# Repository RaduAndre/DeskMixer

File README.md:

# DeskMixer 🎛️

<div align="center">

A **low latency** physical volume mixer with programmable buttons for Windows, inspired by [Deej](https://github.com/omriharel/deej).

**Control your audio with near-instant response and automate actions with real hardware - fully scalable to your needs!**

[Features](#-features) • [Hardware](#-hardware) • [Installation](#-installation) • [Configuration](#-configuration) • [Building](#-building-from-source)

</div>

---

## 🚀 Get Started 

**For Windows users, the simplest way to get up and running is with the pre-compiled executable!**

1.  **Download:** Go to the [**Releases Page**](/RaduAndre/DeskMixer/releases) and download the latest `DeskMixer.exe` file. (no instalation needed)
2. **Configure:** Follow the steps in the [Configuration](#-configuration) section to bind your sliders and program your buttons!

---

## 📸 Gallery

### Modern Software Interface

DeskMixer features a sleek, modern interface with a dark theme and smooth animations designed for intuitive hardware control.

*Clean, modern interface with volume sliders and programmable action buttons*

*Sliding configuration menu for easy customization*

#### Interface Features

**Visual Design:**
- 🎨 **Modern Interface**: Premium glassmorphic design with **customizable accent colors** and animations
- 🪟 **Frameless Window**: Custom title bar with drag-to-move functionality
- 📐 **Scalable Layout**: Automatically adapts to any number of sliders and buttons
- ✨ **Smooth Animations**: Fluid transitions and visual feedback for all interactions

**Volume Sliders:**
- 🎛️ **Visual Scale Indicators**: Each slider displays a scale icon showing the full range
- 🏷️ **Smart Labels**: Automatically display bound applications (e.g., "Master + Spotify")
- 💚 **Hardware Sync**: Sliders animate smoothly when adjusted via hardware with green highlight feedback
- 🔄 **Drag-and-Drop Reordering**: Rearrange sliders to match your preferred layout
- 🖱️ **Click-to-Configure**: Click any slider to open its configuration menu

**Action Buttons:**
- 🎮 **Customizable Grid**: Arrange buttons in any grid size (rows × columns)
- 🔵 **Active State Indicators**: Blue highlight shows which buttons are configured
- ⚡ **Hardware Feedback**: Buttons flash when pressed on the physical device
- 🔄 **Drag-and-Drop**: Reorder buttons including empty placeholder positions
- 📝 **Dynamic Labels**: Button text adjusts to show the configured action

**Configuration Menu:**
- 📱 **Sliding Panel**: Smooth slide-in menu from the right side
- 🎯 **Context-Sensitive**: Different menus for sliders, buttons, and settings
- 🔍 **Live Search**: Browse and add applications with file picker integration
- 📋 **Expandable Sections**: Organized categories with collapsible headers
- ✅ **Visual Selection**: Active bindings highlighted with checkmarks

**Settings & Customization:**
- ⚙️ **General Settings**: Start hidden, Windows startup integration, slider sampling modes
- 📐 **Layout Controls**: Configure button grid dimensions (R×C)
- 🔄 **Reorder Modes**: Toggle swap modes for buttons or sliders independently
- 📊 **Slider Sampling**: Choose between Soft, Normal, or Hard sensitivity modes
- ℹ️ **Version Display**: Build version shown at bottom of settings menu

**Hardware Integration:**
- 🔌 **Real-time Sync**: Slider positions update instantly from hardware movements
- 🎯 **Button Press Feedback**: Visual flash confirms hardware button presses
- 🔄 **Bidirectional Control**: Changes sync between hardware and software
- 🚫 **Read-only Sliders**: UI sliders display-only to prevent conflicts with hardware control

### DIY Hardware Build

*A functional, handcrafted build - proving that professional results don't require a professional workshop!*

---

## ✨ Features

DeskMixer takes physical volume control and supercharges it with macro-like button actions.

### Volume Control
- ⚡ **Low Latency**: Optimized for near-instant response (~10-20ms) with 115200 baud serial communication
- 🎛️ **Physical Sliders**: Control individual application volumes with real hardware sliders
- 📊 **Scalable Design**: Add as many sliders as you need - the software adapts automatically
- 🔊 **Flexible Targets**: Control master volume, microphone, system sounds, or individual apps
- 🎚️ **Adjustable Sensitivity**: Choose between Instant, Responsive, Soft, Normal, or Hard sampling modes
- 💾 **Persistent Settings**: Your configuration is saved between sessions

### Button Actions
- ⌨️ **Custom Keybinds**: Map any keyboard shortcut to physical buttons
- 🎮 **Media Controls**: Play/pause, next/previous track, seek forward/backward
- 🔇 **Mute Controls**: Instant mute/unmute for system, microphone, or specific applications
- 🔀 **Audio Switching**: Switch between audio output devices with a button press
- 🚀 **App Launcher**: Launch or focus applications instantly

### System Integration
- 🪟 **System Tray**: Runs minimized with quick access
- 🔌 **Auto-Detection**: Automatic serial port detection
- 🔄 **Hot-Reload**: Configuration updates in real-time
- 🎯 **Focus Tracking**: Optional control of currently active application

---

## 🎛️ Volume Targets

The software supports multiple volume control modes:

| Target | Description | Use Case |
|--------|-------------|----------|
| 🔊 **Master** | System master volume | Overall volume control |
| 🎤 **Microphone** | Default microphone input | Quick mic adjustments |
| 🔔 **System Sounds** | Windows notification sounds | Silence those pings! |
| ⭐ **Current Application** | Currently focused app | Dynamic control of active app |
| 🎵 **Individual Apps** | Specific applications | Dedicated controls (Spotify, Discord, etc.) |
| ❔ **Unbound** | No assignment | Flexible unassigned slider |
| ❌ **None** | Disabled | Slider inactive |

**Note:** The application list updates automatically based on running audio applications. **The UI scales to accommodate any number of slider bindings you create!**

---

## 🎮 Button Actions

### Media Controls
- ⏯️ **Play/Pause**: Toggle media playback
- ⏭️ **Next Track**: Skip to next media track  
- ⏮️ **Previous Track**: Go to previous media track
- ⏩ **Seek Forward**: Jump forward in current media
- ⏪ **Seek Backward**: Jump backward in current media

### Audio Controls
- 🔊 **Volume Up**: Increase system volume
- 🔉 **Volume Down**: Decrease system volume
- 🔇 **Mute**: Toggle mute for system, microphone, or specific application
- 🔀 **Switch Audio Output**: Switch between available audio output devices*

### Advanced Actions
- ⌨️ **Custom Keybind**: Execute any keyboard shortcut (see [KEYBIND_EXAMPLES.md](KEYBIND_EXAMPLES.md))
- 🚀 **Launch App**: Start or focus specific applications

**Pro Tip:** Combine button actions with specific application targets for powerful workflows. For example:
- Mute Discord specifically with one button
- Launch Spotify and set volume to 50% with another
- Send custom shortcuts to specific apps

**The button configuration UI scales dynamically - add as many buttons as your microcontroller has pins!**

---

## 🔧 Hardware

### Required Components
- **Microcontroller**: ESP32 or compatible Arduino board
- **Sliders**: 4x 10kΩ linear potentiometers (scalable to more)
- **Buttons**: 6x push buttons (scalable to more)
- **Connection**: PCB or breadboard
- **Cable**: USB cable for serial communication

### Default Pin Configuration
You can modify these in the Arduino sketch to match your build:

**Sliders:**
- GPIO 33, 32, 35, 34

**Buttons:**
- GPIO 27, 25, 14, 26, 12, 13

### Expanding Your Build
Want more controls? Simply:
1. Add more potentiometers/buttons to your hardware
2. Update the pin configuration in `arduino/DeskMixer/DeskMixer.ino`
3. Upload the modified firmware
4. The DeskMixer software will automatically detect and configure the new inputs!

### Circuit Explanation

*Wiring diagram showing connections between ESP32, potentiometers, and buttons*

#### Understanding the Circuit

The DeskMixer circuit consists of three main components working together:

**Power Distribution:**
- The ESP32 is powered via USB connection to your computer
- All components share a common ground (GND) connection
- The 3.3V pin from the ESP32 powers the potentiometers

**Potentiometer Connections (Volume Sliders):**
Each potentiometer has three pins:
- **Left pin**: Connected to GND (ground)
- **Middle pin (wiper)**: Connected to ESP32 analog input pins (GPIO 33, 32, 35, 34)
- **Right pin**: Connected to 3.3V power

As you move the slider, the middle pin voltage varies between 0V and 3.3V, which the ESP32 reads as analog values (0-1024). The software then maps these values to volume levels (0-100%).

**Button Connections:**
Each button uses a simple pull-down configuration:
- **One side**: Connected to ESP32 digital input pins (GPIO 27, 25, 14, 26, 12, 13)
- **Other side**: Connected to GND (ground)
- **Internal pull-up resistor**: Enabled in firmware (button reads HIGH when not pressed, LOW when pressed)

**Color Coding in Diagram:**
- **Black**: Ground connections
- **Red**: 3.3V power connections
- **Yellow/Orange/Blue**: Signal wires to ESP32 GPIO pins

#### Important Notes

⚠️ **Analog Pin Limitations**: On ESP32, not all pins support analog reading. Use only ADC1 pins (GPIO 32-39) for potentiometers. Avoid GPIO 25 and 26 for analog input as they're DAC pins.

⚠️ **Voltage Levels**: ESP32 GPIO pins are 3.3V tolerant. Never connect 5V directly to any GPIO pin.

💡 **Wire Gauge**: Use 22-24 AWG wire for connections. Solid core wire works well for breadboard prototyping, while stranded wire is better for the final build.

💡 **Debouncing**: The firmware includes software debouncing for buttons to prevent false triggers. No additional hardware debouncing (capacitors) is needed.

### 3D Models & PCB Files
> **Coming Soon**: 3D printable enclosure models and Gerber files for PCB manufacturing will be added in future updates!

---

## 📦 Installation

### Option 1: Pre-built Executable (Easiest)

1. Download `DeskMixer.exe` from the [Releases](https://github.com/RaduAndre/DeskMixer/releases) page.
2. Run the executable

### Option 2: Run from Source

**Requirements:**
- Python 3.13+
- Arduino IDE
- ESP32 board or compatible Arduino

**Steps:**

1. Clone the repository:
```bash
git clone https://github.com/RaduAndre/DeskMixer.git
cd DeskMixer/src
```

2. Install dependencies:
```bash
pip install -r requirements.txt
```

3. Run the application:
```bash
python main.py
```

### Upload Firmware to Arduino

1. Open `arduino/DeskMixer/DeskMixer.ino` in Arduino IDE
2. Select your board (ESP32) and COM port
3. Upload the sketch
4. The firmware will automatically communicate with DeskMixer

---

## ⚙️ Configuration

### First-Time Setup

1. **Launch DeskMixer**
2. **Connect Hardware**: The application will automatically detect your Arduino's serial port
3. **Configure Sliders**: 
   - Click on any slider to open the configuration menu
   - Select from General options (Master, Microphone, System sounds, Focused application, Unbound)
   - Or choose from Active sounds (currently running applications)
   - Or add custom applications via the search function
   - Multiple applications can be bound to the same slider
4. **Configure Buttons**:
   - Click on any button to open the action menu
   - Select from Media Controls (Play/Pause, Next, Previous, etc.)
   - Configure Mute actions with specific targets
   - Set up custom Keybinds or Launch app actions
   - Changes save automatically

### Slider Configuration

**Binding Options:**
- **General Targets**: Master volume, Microphone, System sounds, Focused application, Unbound
- **Active Sounds**: Dynamically detected running applications with audio
- **Custom Applications**: Add any application via name search or file browser
- **Multiple Bindings**: Bind multiple applications to a single slider for grouped control
- **Smart Labels**: Slider labels automatically update to show all bound applications

**Configuration Menu:**
- Click any slider to open its dedicated configuration menu
- Expandable sections organize options by category
- Active bindings show checkmarks for easy identification
- Right-click custom applications to delete them from the list
- Browse for .exe or .lnk files to add new applications

### Button Configuration

**Available Actions:**

*Media Controls:*
- Play/Pause, Previous, Next
- Volume up/down
- Seek backward/forward

*Advanced Actions:*
- **Mute**: Choose target (Master, Microphone, System sounds, Focused application)
- **Switch Audio Output**: Cycle through devices or select specific output (Speakers, Headphones)
- **Keybind**: Enter custom keyboard shortcuts (see [KEYBIND_EXAMPLES.md](KEYBIND_EXAMPLES.md))
- **Launch app**: Browse and select applications to launch or focus

**Configuration Menu:**
- Click any button to open its action menu
- Expandable items reveal sub-options (e.g., Mute → Master/Microphone/etc.)
- Input fields for Keybind and Launch app actions
- File browser integration for selecting applications
- Active action highlighted with blue indicator

### Layout Customization

**Button Grid:**
- Open Settings menu (gear icon)
- Navigate to Layout → Grid Size
- Enter desired Rows (R) and Columns (C)
- Grid automatically validates against available buttons
- Invalid dimensions flash red with error feedback

**Reordering Elements:**
- Open Settings → Layout → Reorder Elements
- Select "Swap Buttons" or "Swap Sliders" to enter reorder mode
- Drag and drop elements to rearrange them
- Supports sparse layouts (buttons can occupy any grid position)
- Click the reorder option again to exit reorder mode

### Settings Menu

Access via the gear icon in the top-right corner:

**General:**
- **Start Hidden (on tray)**: Launch minimized to system tray
- **Start on Windows startup**: Automatically launch with Windows
- **Slider Sampling**: Adjust hardware response sensitivity
  - **Instant**: Zero-latency mode - no smoothing for immediate response
  - **Responsive**: Minimal smoothing - very fast with slight stabilization
  - **Soft**: Light averaging - balanced response (5 samples)
  - **Normal**: Moderate averaging - smooth control (10 samples)
  - **Hard**: Heavy averaging - very smooth, slower response (20 samples)

**Layout:**
- **Grid Size**: Configure button grid dimensions
- **Accent Color**: Customize the UI with 'Default' (Teal) or any custom color via the picker
- **Reorder Elements**: Enable drag-and-drop for buttons or sliders

### System Tray
- **Double-click** tray icon: Show/hide main window
- **Right-click** tray icon: Quick actions menu
- Window automatically minimizes to tray when closed

---

## 🏗️ Building from Source

Create your own executable using either method:

### PyInstaller (Faster)
```bash
cd src
python build_app.py
```

### Nuitka (More Optimized)
```bash
cd src
python build_nuitka.py
```

Built executables will appear in `src/build/dist/`

---

## 🎨 About the Hardware Build

The device shown in the gallery was handcrafted with basic tools and materials - no fancy workshop required! It's a testament that functional, effective hardware doesn't need to be professionally manufactured. The beauty of this project is in its functionality and the satisfaction of building something yourself.

**DIY Philosophy:** This project embraces the maker spirit - it's about creating tools that work for YOU, not winning beauty contests. If it controls your volume and makes your workflow better, it's perfect.

---

## 🛠️ Customization & Scalability

DeskMixer is designed to grow with your needs:

### Hardware Scaling
- **Start small**: 2 sliders and 2 buttons  
- **Go big**: 16+ sliders and 20+ buttons
- **Mix it up**: Combine sliders, buttons, rotary encoders, or other inputs

The software automatically adapts to whatever hardware configuration you define in the Arduino firmware!

### Software Flexibility
- Configure targets per-slider/button
- Create complex automation chains
- Save multiple profiles (future feature)

---

## 📝 Keybind Examples

For comprehensive keybind examples and syntax, see [KEYBIND_EXAMPLES.md](KEYBIND_EXAMPLES.md)

---

## 🤝 Contributing

Contributions are welcome! Whether it's:
- 🐛 Bug reports
- 💡 Feature suggestions  
- 📝 Documentation improvements
- 🔧 Code contributions
- 📸 Sharing your build

Feel free to open an issue or submit a pull request!

---

## 📄 License

This project is open source. Check the [LICENSE](LICENSE) file for details.

---

## 🙏 Acknowledgments

- Inspired by [Deej](https://github.com/omriharel/deej) by Omri Harel
- Built with passion for makers and tinkerers everywhere
- Special thanks to everyone who builds DIY hardware and shares their projects!

---

## 📞 Support

- **Issues**: [GitHub Issues](https://github.com/RaduAndre/DeskMixer/issues)
- **Discussions**: [GitHub Discussions](https://github.com/RaduAndre/DeskMixer/discussions)

---

<div align="center">

**Made with 🎛️ by makers, for makers**

Star ⭐ this repo if you find it useful! You can also support further development [buying me a Coffe ☕](https://ko-fi.com/andreiradu).

</div>

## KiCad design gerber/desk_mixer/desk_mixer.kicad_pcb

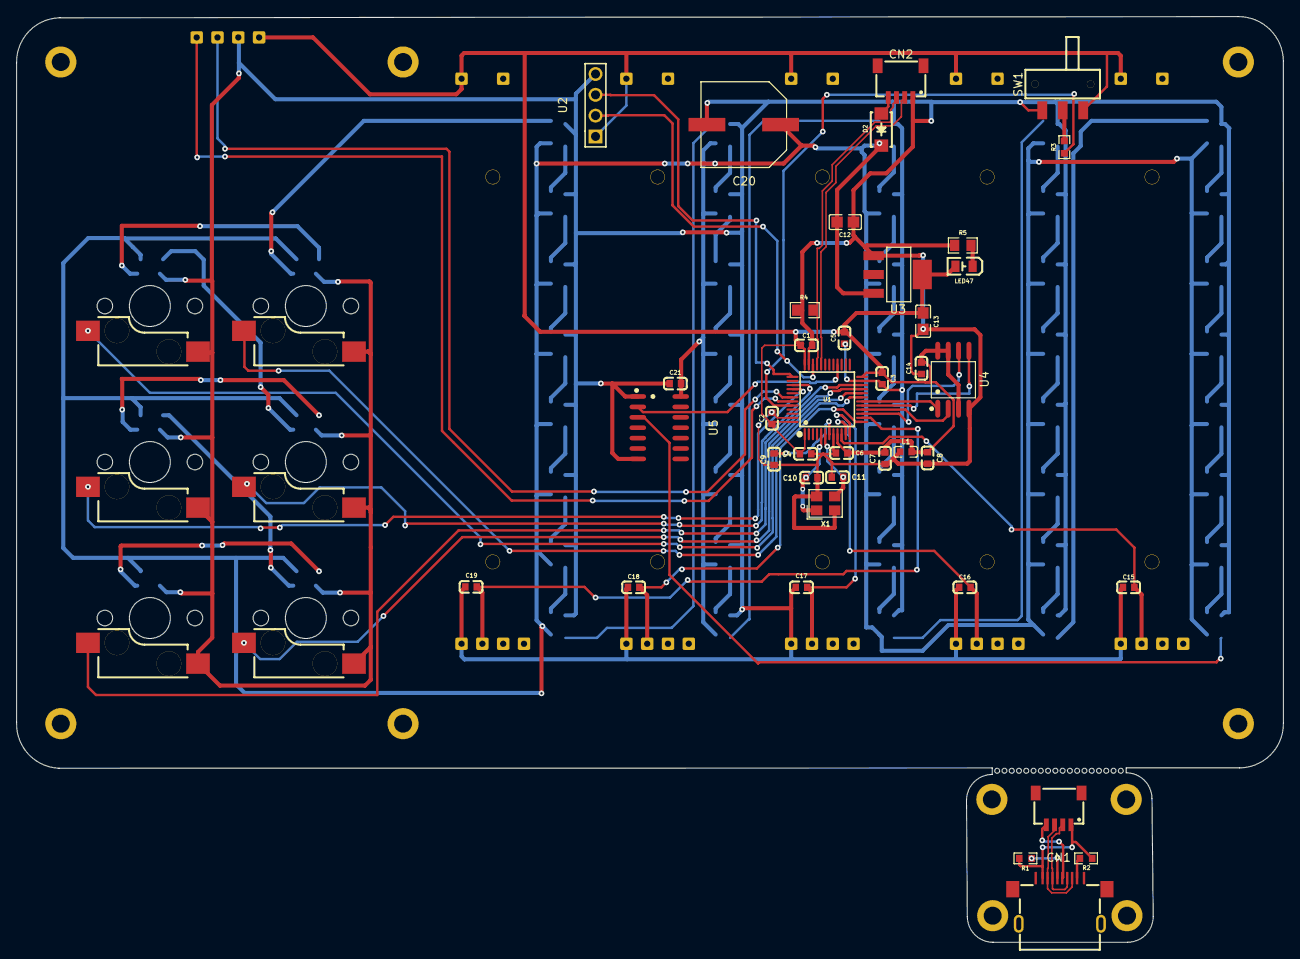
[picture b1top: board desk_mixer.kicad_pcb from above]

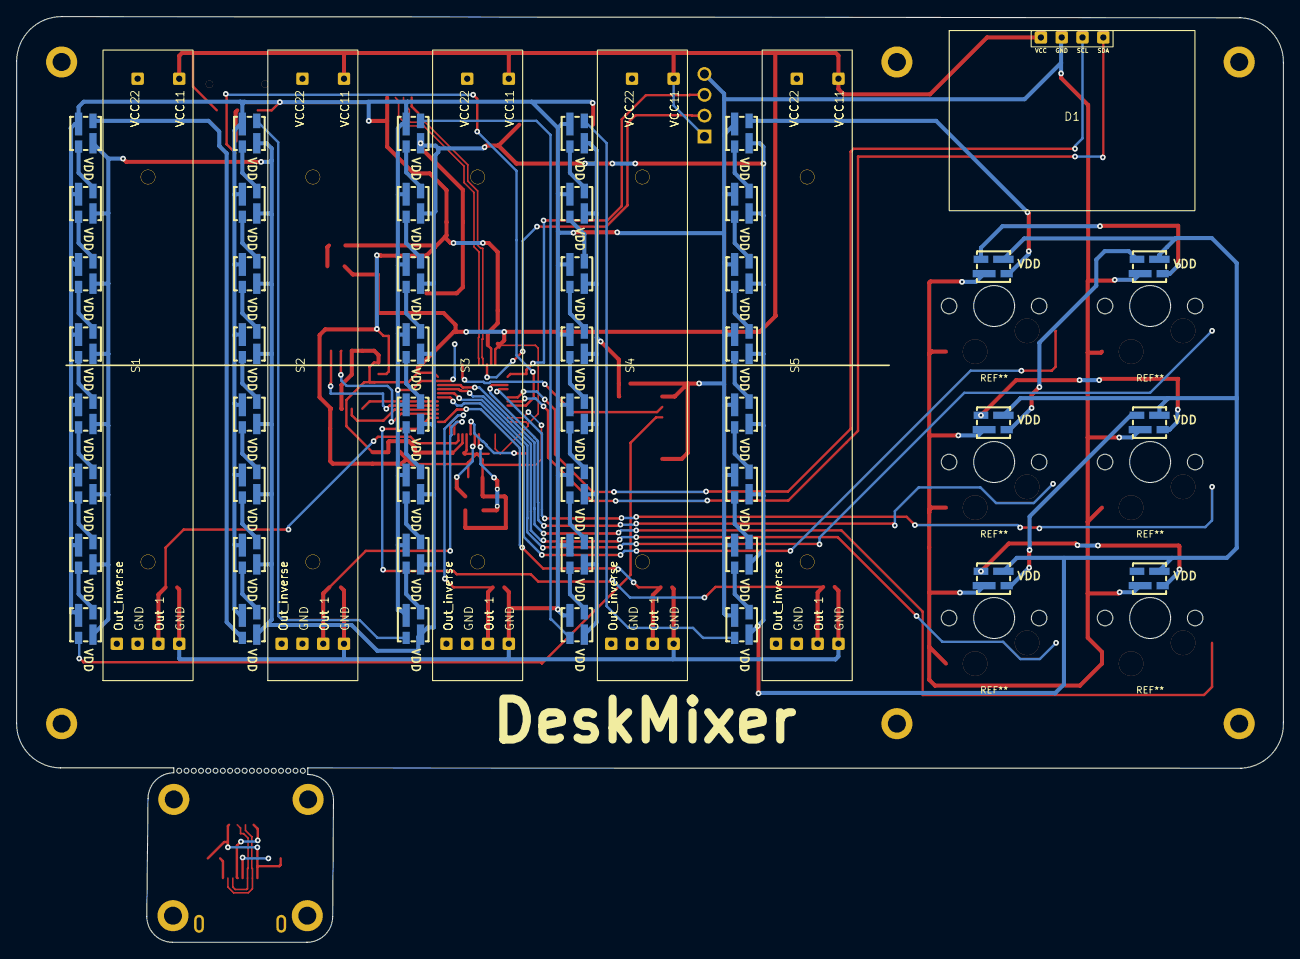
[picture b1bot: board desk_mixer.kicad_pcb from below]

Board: 2 copper layers, 154.7 x 113.0 mm, 97 parts (52 on the bottom side), 84 nets.

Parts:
C1, C2, C3, C4, C6, C9, C14, C15, C16, C17, C18, C19, C21: 100n; C0603
C5: 10u; C0603
C7, C8: 1uF; C0603
C10, C11: 10p; C0603
C12, C13: 22u; C0805
C20: BXJ 10V1000uF; CAP-SMD_BD10.0-L10.3-W10.3-FD
CN1, CN2: SM04B-SRSS-TB (LF)(SN); CONN-SMD_4P-P1.00_SM04B-SRSS-TB-LF-SN
D1: screen
D2: SS14; SMA_L4.2-W2.6-LS5.0-RD_1
Kal1, Kal2, Kal3, Kal4, Kal5, Kal6: CPG151101S11-2_C49352235; TH_L10.9-W5.9-CPG151101S11-2
L1: Ferritebead; L0603
LED1, LED2, LED3, LED4, LED5, LED6, LED7, LED8, LED9, LED10, LED11, LED12, LED13, LED14, LED15, LED16, LED17, LED18, LED19, LED20, LED21, LED22, LED23, LED24, LED25, LED26, LED27, LED28, LED29, LED30, LED31, LED32, LED33, LED34, LED35, LED36, LED37, LED38, LED39, LED40, LED41, LED42, LED43, LED44, LED45, LED46: SK6812MINI; LED-SMD_4P-L3.7-W3.5-P1.75-BR-SK6812MINI
LED47: Red led; LED0805-R-RD_RED
R1, R2: 5.1k; R0603
R3: 10k; R0603
R4, R5: 1.5k; R0805
S1, S2, S3, S4, S5: b103
SW1: MST-12D18G4 SPDT SLIDE SWITCH; SW-SMD_MST-12D18G4-SPDT-SLIDE-SWITCH
U1: STM32F103C8T6; LQFP-48_L7.0-W7.0-P0.50-LS9.0-BL
U2: 2.54-1*4; HDR-TH_4P-P2.54-V-M-1
U3: AMS1117-3.3; SOT-223-3_L6.5-W3.4-P2.30-LS7.0-BR
U4: GD25Q64ESIG; SOP-8_L5.3-W5.3-P1.27-LS8.0-BL
U5: SN74AHCT125DR; SOIC-14_L8.7-W3.9-P1.27-LS6.0-BL
USB1: USB-PG 10PIN 040; USB-SMD-LIGHTNING_USB-PG
X1: X322516MMB4SI; CRYSTAL-SMD_4P-L3.2-W2.5-BL

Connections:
+3.3V: C1.2, C2.2, C3.2, C4.2, C5.2, C6.2, C7.2, C8.2, C13.1, C14.2, D1.1 (VCC), L1.2, LED47.1 (+), S1.6 (VCC1), S2.6 (VCC1), S3.6 (VCC1), S4.6 (VCC1), S5.6 (VCC1), SW1.1, U1.1 (VBAT), U1.9 (VDDA), U1.24 (VDD_1), U1.36 (VDD_2), U1.48 (VDD_3), U2.1, U3.4 (VOUT), U4.3 (WP#(IO2)), U4.7 (HOLD#(IO3)), U4.8 (VCC)
/ACC1: R1.2, USB1.5 (ACC1)
/ACC2: R2.2, USB1.9 (ACC2)
/Button_1: Kal1.1, U1.19 (PB1)
/Button_2: Kal2.1, U1.20 (PB2)
/Button_3: Kal3.1, U1.39 (PB3)
/Button_4: Kal4.1, U1.40 (PB4)
/Button_5: Kal5.1, U1.21 (PB10)
/Button_6: Kal6.1, U1.22 (PB11)
/D+: CN1.3, USB1.3 (DP1), USB1.8 (DP2)
/D-: CN1.2, USB1.4 (DN1), USB1.7 (DN2)
/GPIO out: U1.18 (PB0), U4.1 (~CS)
/LED_CMD 3.3v: U1.28 (PB15), U5.2 (1A)
/LED_CMD 5v: LED1.1 (DIN), U5.3 (1Y)
/MISO: U1.16 (PA6), U4.2 (SO(IO1))
/MOSI: U1.17 (PA7), U4.5 (SI(IO0))
/NRST: C9.1, U1.7 (NRST)
/OSC_IN: C10.1, U1.5 (PD0-OSC_IN), X1.1 (OSC1)
/OSC_OUT: C11.1, U1.6 (PD1-OSC_OUT), X1.3 (OSC2)
/SCK: U1.15 (PA5), U4.6 (SCLK)
/SLIDER_1: C15.1, S1.3 (Out), U1.10 (PA0-WKUP)
/SLIDER_2: C16.1, S2.3 (Out), U1.11 (PA1)
/SLIDER_3: C17.1, S3.3 (Out), U1.12 (PA2)
/SLIDER_4: C18.1, S4.3 (Out), U1.13 (PA3)
/SLIDER_5: C19.1, S5.3 (Out), U1.14 (PA4)
/SW Boot: R3.1, U1.44 (BOOT0)
/SWIDO: U1.34 (PA13), U2.2
/USB_D+: CN2.3, R4.2, U1.33 (PA12)
/USB_D-: CN2.2, U1.32 (PA11)
GND: C1.1, C2.1, C3.1, C4.1, C5.1, C6.1, C7.1, C8.1, C9.2, C10.2, C11.2, C12.2, C13.2, C14.1, C15.2, C16.2, C17.2, C18.2, C19.2, C20.2, C21.2, CN2.1, D1.2 (GND), Kal1.2, Kal2.2, Kal3.2, Kal4.2, Kal5.2, Kal6.2, L1.1, LED1.4 (GND), LED2.4 (GND), LED3.4 (GND), LED4.4 (GND), LED5.4 (GND), LED6.4 (GND), LED7.4 (GND), LED8.4 (GND), LED9.4 (GND), LED10.4 (GND), LED11.4 (GND), LED12.4 (GND), LED13.4 (GND), LED14.4 (GND), LED15.4 (GND), LED16.4 (GND), LED17.4 (GND), LED18.4 (GND), LED19.4 (GND), LED20.4 (GND), LED21.4 (GND), LED22.4 (GND), LED23.4 (GND), LED24.4 (GND), LED25.4 (GND), LED26.4 (GND), LED27.4 (GND), LED28.4 (GND), LED29.4 (GND), LED30.4 (GND), LED31.4 (GND), LED32.4 (GND), LED33.4 (GND), LED34.4 (GND), LED35.4 (GND), LED36.4 (GND), LED37.4 (GND), LED38.4 (GND), LED39.4 (GND), LED40.4 (GND), LED41.4 (GND), LED42.4 (GND), LED43.4 (GND), LED44.4 (GND), LED45.4 (GND), LED46.4 (GND), R4.1, R5.1, S1.4 (GND), S2.4 (GND), S3.4 (GND), S4.4 (GND), S5.4 (GND), SW1.3, U1.8 (VSSA), U1.23 (VSS_1), U1.35 (VSS_2), U1.47 (VSS_3), U2.4, U3.1 (GND), U4.4 (VSS), U5.1 (~1OE), U5.7 (GND), X1.2 (GND), X1.4 (GND)
GND2: CN1.1, R1.1, R2.1, USB1.2 (GND)
unnamed: LED1.3 (DOUT), LED2.1 (DIN)
unnamed: LED2.3 (DOUT), LED3.1 (DIN)
unnamed: LED3.3 (DOUT), LED4.1 (DIN)
unnamed: LED4.3 (DOUT), LED5.1 (DIN)
unnamed: LED5.3 (DOUT), LED6.1 (DIN)
unnamed: LED6.3 (DOUT), LED7.1 (DIN)
unnamed: LED7.3 (DOUT), LED8.1 (DIN)
unnamed: LED8.3 (DOUT), LED9.1 (DIN)
unnamed: LED9.3 (DOUT), LED10.1 (DIN)
unnamed: LED10.3 (DOUT), LED11.1 (DIN)
unnamed: LED11.3 (DOUT), LED12.1 (DIN)
unnamed: LED12.3 (DOUT), LED13.1 (DIN)
unnamed: LED13.3 (DOUT), LED14.1 (DIN)
unnamed: LED14.3 (DOUT), LED15.1 (DIN)
unnamed: LED15.3 (DOUT), LED16.1 (DIN)
unnamed: LED16.3 (DOUT), LED17.1 (DIN)
unnamed: LED17.3 (DOUT), LED18.1 (DIN)
unnamed: LED18.3 (DOUT), LED19.1 (DIN)
unnamed: LED19.3 (DOUT), LED20.1 (DIN)
unnamed: LED20.3 (DOUT), LED21.1 (DIN)
unnamed: LED21.3 (DOUT), LED22.1 (DIN)
unnamed: LED22.3 (DOUT), LED23.1 (DIN)
unnamed: LED23.3 (DOUT), LED24.1 (DIN)
unnamed: LED24.3 (DOUT), LED25.1 (DIN)
unnamed: LED25.3 (DOUT), LED26.1 (DIN)
unnamed: LED26.3 (DOUT), LED27.1 (DIN)
unnamed: LED27.3 (DOUT), LED28.1 (DIN)
unnamed: LED28.3 (DOUT), LED29.1 (DIN)
unnamed: LED29.3 (DOUT), LED30.1 (DIN)
unnamed: LED30.3 (DOUT), LED31.1 (DIN)
unnamed: LED31.3 (DOUT), LED32.1 (DIN)
unnamed: LED32.3 (DOUT), LED33.1 (DIN)
unnamed: LED33.3 (DOUT), LED34.1 (DIN)
unnamed: LED34.3 (DOUT), LED35.1 (DIN)
unnamed: LED35.3 (DOUT), LED36.1 (DIN)
unnamed: LED36.3 (DOUT), LED37.1 (DIN)
unnamed: LED37.3 (DOUT), LED38.1 (DIN)
unnamed: LED38.3 (DOUT), LED39.1 (DIN)
unnamed: LED39.3 (DOUT), LED40.1 (DIN)
unnamed: LED40.3 (DOUT), LED41.1 (DIN)
unnamed: LED41.3 (DOUT), LED42.1 (DIN)
unnamed: LED42.3 (DOUT), LED43.1 (DIN)
unnamed: LED43.3 (DOUT), LED44.1 (DIN)
unnamed: LED44.3 (DOUT), LED45.1 (DIN)
unnamed: LED45.3 (DOUT), LED46.1 (DIN)
unnamed: LED47.2 (-), R5.2
unnamed: R3.2, SW1.2
SCL: D1.3 (SCl), U1.42 (PB6)
SDA: D1.4 (SDA), U1.43 (PB7)
SWCLC: U1.37 (PA14), U2.3
VBUS: C12.1, C20.1, C21.1, D2.1 (K), LED1.2 (VDD), LED2.2 (VDD), LED3.2 (VDD), LED4.2 (VDD), LED5.2 (VDD), LED6.2 (VDD), LED7.2 (VDD), LED8.2 (VDD), LED9.2 (VDD), LED10.2 (VDD), LED11.2 (VDD), LED12.2 (VDD), LED13.2 (VDD), LED14.2 (VDD), LED15.2 (VDD), LED16.2 (VDD), LED17.2 (VDD), LED18.2 (VDD), LED19.2 (VDD), LED20.2 (VDD), LED21.2 (VDD), LED22.2 (VDD), LED23.2 (VDD), LED24.2 (VDD), LED25.2 (VDD), LED26.2 (VDD), LED27.2 (VDD), LED28.2 (VDD), LED29.2 (VDD), LED30.2 (VDD), LED31.2 (VDD), LED32.2 (VDD), LED33.2 (VDD), LED34.2 (VDD), LED35.2 (VDD), LED36.2 (VDD), LED37.2 (VDD), LED38.2 (VDD), LED39.2 (VDD), LED40.2 (VDD), LED41.2 (VDD), LED42.2 (VDD), LED43.2 (VDD), LED44.2 (VDD), LED45.2 (VDD), LED46.2 (VDD), U3.3 (VIN), U5.14 (VCC)
VBUS2: CN1.4, USB1.6 (PWR)
VBUS_Z: CN2.4, D2.2 (A)

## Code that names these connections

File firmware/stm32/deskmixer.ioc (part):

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Mcu.Name=STM32F103C(8-B)Tx
Mcu.Package=LQFP48
Mcu.UserName=STM32F103C8Tx
PA0-WKUP.Signal=ADCx_IN0
PA1.Signal=ADCx_IN1
PA11.Mode=Device
PA11.Signal=USB_DM
PA12.Mode=Device
PA12.Signal=USB_DP
PA13.Mode=Serial_Wire
PA13.Signal=SYS_JTMS-SWDIO
PA14.Mode=Serial_Wire
PA14.Signal=SYS_JTCK-SWCLK
PA2.Signal=ADCx_IN2
PA3.Signal=ADCx_IN3
PA4.Signal=ADCx_IN4
PA5.Mode=Full_Duplex_Master
PA5.Signal=SPI1_SCK
PA6.Mode=Full_Duplex_Master
PA6.Signal=SPI1_MISO
PA7.Mode=Full_Duplex_Master
PA7.Signal=SPI1_MOSI
PB0.GPIOParameters=PinState,GPIO_Label
PB0.GPIO_Label=FLASH_CS
PB0.PinState=GPIO_PIN_SET
PB0.Signal=GPIO_Output
PB1.GPIOParameters=GPIO_PuPd
PB1.GPIO_PuPd=GPIO_PULLUP
PB1.Signal=GPIO_Input
PB10.GPIOParameters=GPIO_PuPd
PB10.GPIO_PuPd=GPIO_PULLUP
PB10.Signal=GPIO_Input
PB11.GPIOParameters=GPIO_PuPd
PB11.GPIO_PuPd=GPIO_PULLUP
PB11.Signal=GPIO_Input
PB13.Mode=TX_Only_Simplex_Unidirect_Master
PB13.Signal=SPI2_SCK
PB15.Mode=TX_Only_Simplex_Unidirect_Master
PB15.Signal=SPI2_MOSI
PB2.GPIOParameters=GPIO_PuPd
PB2.GPIO_PuPd=GPIO_PULLUP
PB2.Signal=GPIO_Input
PB3.GPIOParameters=GPIO_PuPd
PB3.GPIO_PuPd=GPIO_PULLUP
PB3.Signal=GPIO_Input
PB4.GPIOParameters=GPIO_PuPd
PB4.GPIO_PuPd=GPIO_PULLUP
PB4.Signal=GPIO_Input
PB6.Mode=I2C
PB6.Signal=I2C1_SCL
PB7.Mode=I2C
PB7.Signal=I2C1_SDA
PD0-OSC_IN.Mode=HSE-External-Oscillator
PD0-OSC_IN.Signal=RCC_OSC_IN
PD1-OSC_OUT.Mode=HSE-External-Oscillator
PD1-OSC_OUT.Signal=RCC_OSC_OUT
RCC.HSEDivPLL=RCC_HSE_PREDIV_DIV2
RCC.HSE_VALUE=16000000
RCC.SYSCLKFreq_VALUE=48000000
RCC.SYSCLKSource=RCC_SYSCLKSOURCE_PLLCLK
board=custom

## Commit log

2025-10-23 Create LICENSE
2025-10-23 Fixed a bug in config_manager where on windows startup it would not load the config properly.
2025-10-23 Changed project structure, moving source files to 'src/' directory
2025-10-23 Project restructuring: Move all source files into 'src' directory
2025-10-23 Updated the requirements.txt file with new dependencies. Updated README.md to reflect recent changes. Added functionality for app bindings for buttons.
2025-10-23 Updated README.md and fixed bugs in audio_manager.py and main.py Updated actions to enable app launch binding functionality.
2025-10-23 Fixed some bugs and updated build app
2025-10-23 Fixed a bug where the app would not start maximized when not set to start hidden in tray.
2025-10-23 Fixed a bug where the main window would not start maximized when not set to start in tray.
2025-10-23 Rebuilt some modules
2025-10-23 Fixed a bug where if there were 2 window instances with the same name example firefox.exe it wont update the sond of both of them.
2025-10-23 Fixed a bug where if I changed the output device, the volume changes were done to the previous output.
2025-10-24 Implemented the function to detect device disconnection and automatic reconnection.
2025-10-24 Added the compiler to nuitka for better compilation/performance. I also letf pyinstaller.
2025-10-26 Added the functionality to switch the audio output and changed the behaviour of the x button on the window to close the application not minimise. Added better com handling on audio manager.
2025-10-26 fixed a bug where a powershell was appearing during audio output switch
2025-10-27 When trying to launch the app a second time while its running it brings that on focus.
2025-10-27 Using only windows at this time.
2025-10-27 Ui update.
2025-10-27 Changed the behaviour of the connection to the device, it now tries to autoconnect to the device via handshake. And handles disconection and automatic reconection.
2025-10-28 Added more error handling functionality.
2025-10-28 Changed the save location of the config file and the error.log.
2025-10-28 Added a button to open the config and log folder.
2025-10-28 Updated so when connected succesfully to a device saves that connection to the config.json.
2025-10-28 Changed the behaviour of the config tab, instead of manually creating the fields and assigning the variables it auto creates the fields and assigns the variable names. Fully adaptable to the configur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
2025-10-28 Ui update
2025-11-06 Added the option to browse for any other application on the pc.
2025-11-06 Removed the button for search, instead now it searches on clicking on the input field, and better shortcut handling.
2025-11-06 Added the record functionality for the keybind action.
2025-11-08 specifieed pycaw version
2025-11-09 updated pycaw version to 20251023 and changed audio output switchng protocol from using audiodevicecmd to pycaw
2025-11-09 changed the build files location
2025-11-09 Refactoring
2025-11-11 Added selector for slider to save the browsed app name
2025-11-30 Refactoring for audio manager and separation for specific functions. Removed emojis and emoji handling.
2025-12-05 Fixed a bug where mute wouldnt work. Crated mockups for the future ui.
2025-12-08 Created mock ui for future implementation
2025-12-08 Partial implementation of the new ui
2025-12-10 Full implementation of the new ui
2025-12-11 Audio controller optimisation and button handler smoothing. Ui optimisations.
2025-12-12 Optimize latency (~200ms reduction), fix action mappings, enhance mute menu
2025-12-12 Fixed ui slider sync on launch with the board. Removed tkinter imports.
2025-12-14 Change 'Ultra-Low Latency' to 'Low Latency' in README
2025-12-15 implement custom accent color picker - Replace preset color list with "Default" (Teal) and "Select new color" options - Add [ColorPickerWindow].with Hue slider, Sat/Val map, and Hex syncing - Update 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
2025-12-15 Bugfix
2025-12-17 Refactor MenuBuilder, Add Volume Sync & Screen Menu
    Changes:
    Refactor: Split
    MenuBuilder
    logic into dedicated SettingsMenu, SliderMenu, and
    ButtonMenu
    components in src/ui2/components/menu/.
2025-12-17 Added dependency-submission.yml
2026-04-22 Added gerber files, and created firmware for stm32. Changed the value parsing.
2026-04-22 Change license to Creative Commons Attribution-NonCommercial
    Updated license from MIT to Creative Commons Attribution-NonCommercial 4.0 International Public License, including detailed terms and conditions.
2026-05-04 feat: implement STM32 slider ADC drivers, serial communication protocol, and Python interface for device data parsing and testing
2026-05-09 feat: implement SK6812 LED driver and animation system for DeskMixer firmware
2026-05-09 Improved parameter parsing and implemented partial led configurations
2026-05-10 Fixed led and oled slider based reading procentages and slider data sampler.
2026-05-11 Fixed a bug where config gets corrupted
2026-05-17 implement board communication layer and expand STM32 firmware functionality
